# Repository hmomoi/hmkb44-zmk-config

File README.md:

# hmkb44 のページ

44キーのキーボード「hmkb44」の作成資材のページです。

主に、zmkファームウェアの管理と、KiCadの設計資材をおいています。

# 目指すキーボード
* 40%キーボード（EPOMAKER TH40を参考に）
* Bluetoothで接続
* LEDチカチカ
* charlieplexの実験

このくらいを目指して作ってます。
seeeduino_xiao_ble を使ってイロイロ実験してみたくて作成しました。
# レイアウト

# 回路

# 参照したnote
* https://note.com/pooh_polo/n/n2a34a922b4c8 (zmk firmwareの書き方)

# 参照したgithub
* https://github.com/te9no/zmk-config-GeaconSolstice/blob/main/boards/shields/GeaconSolstice/Solstice.keymap
* https://github.com/mctechnology17/zmk-config
* https://github.com/te9no/zmk-config-title72 （charlieplexのダイオードの向きが逆）
* https://github.com/HookyKB/round-robin-schematics (charlieplexのschematicが公開されている)
* https://github.com/mentako-ya/zmk-config-mtk64/tree/master (Layer rgbled widget を参考)

# キーマップ

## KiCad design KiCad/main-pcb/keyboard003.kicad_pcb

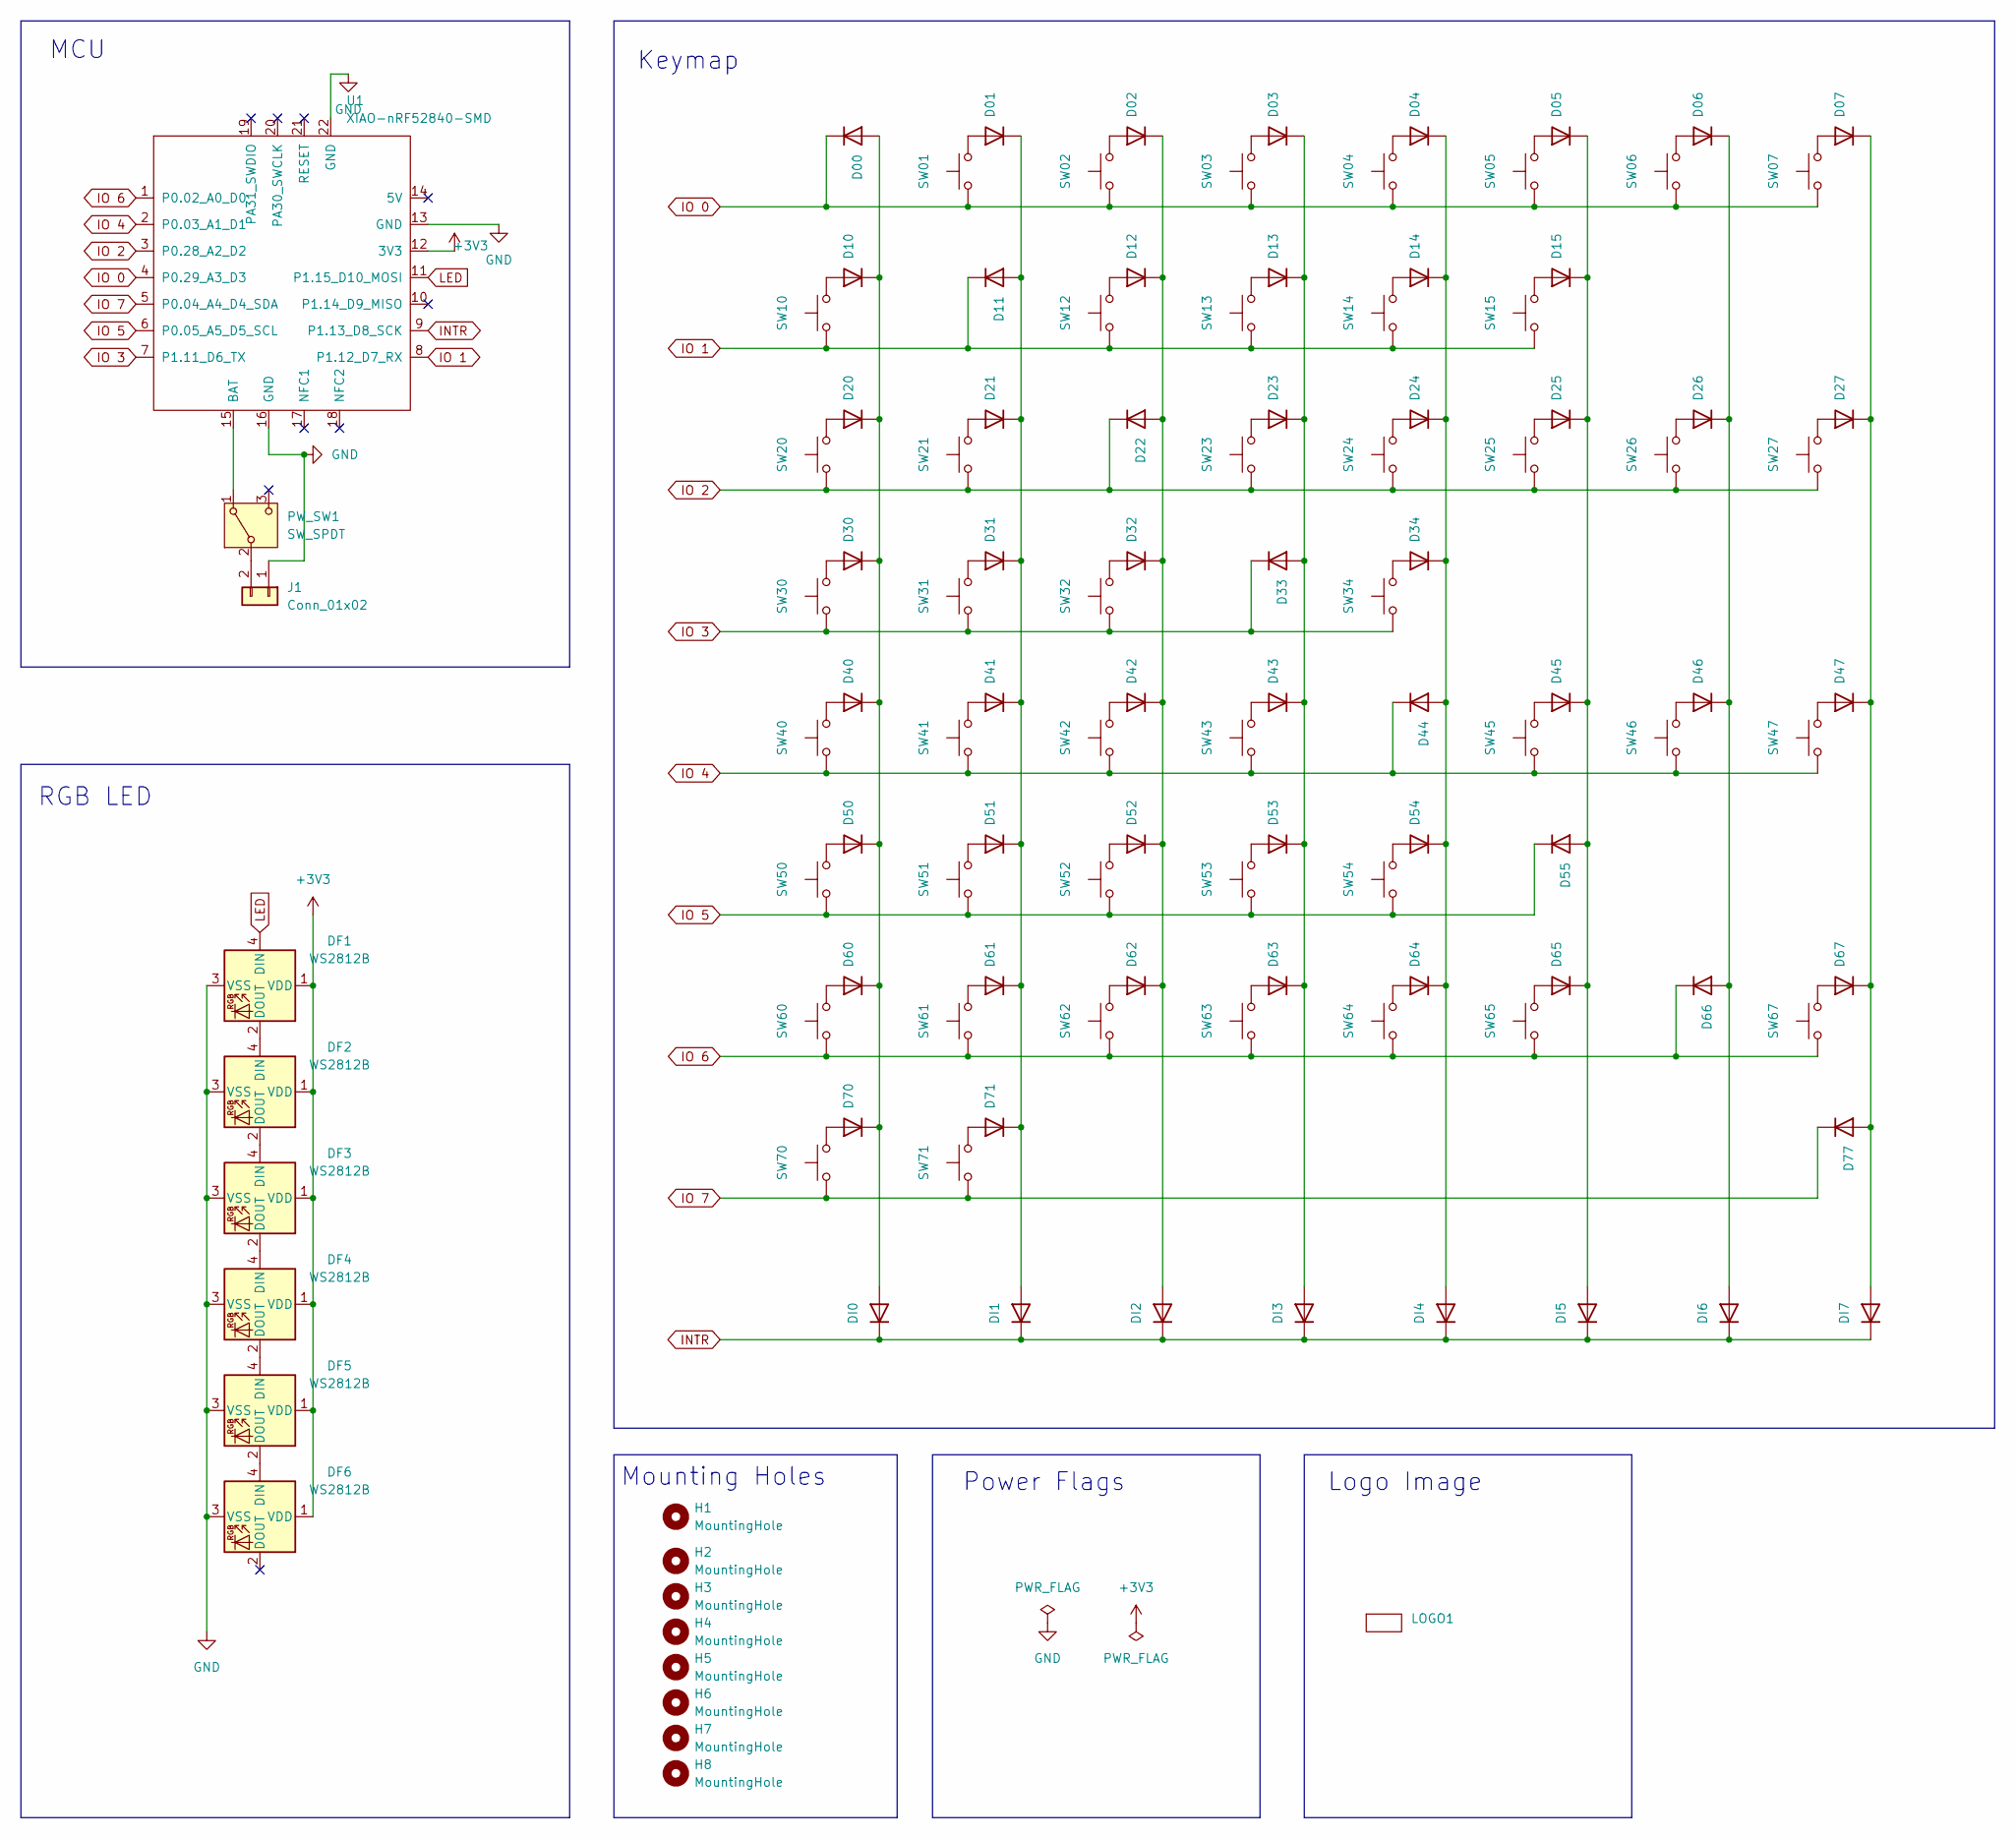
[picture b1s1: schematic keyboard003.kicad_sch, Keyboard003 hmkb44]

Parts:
D00, D01, D02, D03, D04, D05, D06, D07, D10, D11, D12, D13, D14, D15, D20, D21, D22, D23, D24, D25, D26, D27, D30, D31, D32, D33, D34, D40, D41, D42, D43, D44, D45, D46, D47, D50, D51, D52, D53, D54, D55, D60, D61, D62, D63, D64, D65, D66, D67, D70, D71, D77: 1N4148W; D_SOD-123; LCSC C81598
DF1, DF2, DF3, DF4, DF5, DF6: WS2812B; LED_WS2812B_PLCC4_5.0x5.0mm_P3.2mm
DI0, DI1, DI2, DI3, DI4, DI5, DI6, DI7: 1N4148W; D_SOD-123; LCSC C81598
H1, H2, H3, H4, H5, H6, H7, H8: MountingHole; MountingHole_2.2mm_M2
J1: Conn_01x02; JST_PH_S2B-PH-K_1x02_P2.00mm_Horizontal
LOGO1: LOGO
PW_SW1: SW_SPDT; SS-12D01G3
SW01, SW15: SW_Push; CherryMX_Hotswap_1.5u
SW02, SW03, SW04, SW05, SW06, SW07, SW10, SW12, SW13, SW14, SW21, SW23, SW24, SW25, SW26, SW27, SW30, SW31, SW32, SW41, SW42, SW43, SW45, SW46, SW47, SW50, SW51, SW52, SW53, SW64: SW_Push; CherryMX_Hotswap_1u
SW20, SW54: SW_Push; CherryMX_Hotswap_1.75u
SW34, SW63, SW65: SW_Push; CherryMX_Hotswap_2.25u
SW40, SW60, SW61, SW62, SW67, SW70, SW71: SW_Push; CherryMX_Hotswap_1.25u
U1: XIAO-nRF52840-SMD

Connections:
+3V3: DF1.1 (VDD), DF2.1 (VDD), DF3.1 (VDD), DF4.1 (VDD), DF5.1 (VDD), DF6.1 (VDD), U1.12 (3V3)
GND: DF1.3 (VSS), DF2.3 (VSS), DF3.3 (VSS), DF4.3 (VSS), DF5.3 (VSS), DF6.3 (VSS), J1.1, U1.13 (GND), U1.16 (GND), U1.22 (GND)
INTR: DI0.1 (K), DI1.1 (K), DI2.1 (K), DI3.1 (K), DI4.1 (K), DI5.1 (K), DI6.1 (K), DI7.1 (K), U1.9 (P1.13_D8_SCK)
IO 0: D00.1 (K), SW01.1, SW02.1, SW03.1, SW04.1, SW05.1, SW06.1, SW07.1, U1.4 (P0.29_A3_D3)
IO 1: D11.1 (K), SW10.1, SW12.1, SW13.1, SW14.1, SW15.1, U1.8 (P1.12_D7_RX)
IO 2: D22.1 (K), SW20.1, SW21.1, SW23.1, SW24.1, SW25.1, SW26.1, SW27.1, U1.3 (P0.28_A2_D2)
IO 3: D33.1 (K), SW30.1, SW31.1, SW32.1, SW34.1, U1.7 (P1.11_D6_TX)
IO 4: D44.1 (K), SW40.1, SW41.1, SW42.1, SW43.1, SW45.1, SW46.1, SW47.1, U1.2 (P0.03_A1_D1)
IO 5: D55.1 (K), SW50.1, SW51.1, SW52.1, SW53.1, SW54.1, U1.6 (P0.05_A5_D5_SCL)
IO 6: D66.1 (K), SW60.1, SW61.1, SW62.1, SW63.1, SW64.1, SW65.1, SW67.1, U1.1 (P0.02_A0_D0)
IO 7: D77.1 (K), SW70.1, SW71.1, U1.5 (P0.04_A4_D4_SDA)
LED: DF1.4 (DIN), U1.11 (P1.15_D10_MOSI)
unnamed: D00.2 (A), D10.1 (K), D20.1 (K), D30.1 (K), D40.1 (K), D50.1 (K), D60.1 (K), D70.1 (K), DI0.2 (A)
unnamed: D01.2 (A), SW01.2
unnamed: D01.1 (K), D11.2 (A), D21.1 (K), D31.1 (K), D41.1 (K), D51.1 (K), D61.1 (K), D71.1 (K), DI1.2 (A)
unnamed: D02.2 (A), SW02.2
unnamed: D02.1 (K), D12.1 (K), D22.2 (A), D32.1 (K), D42.1 (K), D52.1 (K), D62.1 (K), DI2.2 (A)
unnamed: D03.2 (A), SW03.2
unnamed: D03.1 (K), D13.1 (K), D23.1 (K), D33.2 (A), D43.1 (K), D53.1 (K), D63.1 (K), DI3.2 (A)
unnamed: D04.2 (A), SW04.2
unnamed: D04.1 (K), D14.1 (K), D24.1 (K), D34.1 (K), D44.2 (A), D54.1 (K), D64.1 (K), DI4.2 (A)
unnamed: D05.2 (A), SW05.2
unnamed: D05.1 (K), D15.1 (K), D25.1 (K), D45.1 (K), D55.2 (A), D65.1 (K), DI5.2 (A)
unnamed: D06.2 (A), SW06.2
unnamed: D06.1 (K), D26.1 (K), D46.1 (K), D66.2 (A), DI6.2 (A)
unnamed: D07.2 (A), SW07.2
unnamed: D07.1 (K), D27.1 (K), D47.1 (K), D67.1 (K), D77.2 (A), DI7.2 (A)
unnamed: D10.2 (A), SW10.2
unnamed: D12.2 (A), SW12.2
unnamed: D13.2 (A), SW13.2
unnamed: D14.2 (A), SW14.2
unnamed: D15.2 (A), SW15.2
unnamed: D20.2 (A), SW20.2
unnamed: D21.2 (A), SW21.2
unnamed: D23.2 (A), SW23.2
unnamed: D24.2 (A), SW24.2
unnamed: D25.2 (A), SW25.2
unnamed: D26.2 (A), SW26.2
unnamed: D27.2 (A), SW27.2
unnamed: D30.2 (A), SW30.2
unnamed: D31.2 (A), SW31.2
unnamed: D32.2 (A), SW32.2
unnamed: D34.2 (A), SW34.2
unnamed: D40.2 (A), SW40.2
unnamed: D41.2 (A), SW41.2
unnamed: D42.2 (A), SW42.2
unnamed: D43.2 (A), SW43.2
unnamed: D45.2 (A), SW45.2
unnamed: D46.2 (A), SW46.2
unnamed: D47.2 (A), SW47.2
unnamed: D50.2 (A), SW50.2
unnamed: D51.2 (A), SW51.2
unnamed: D52.2 (A), SW52.2
unnamed: D53.2 (A), SW53.2
unnamed: D54.2 (A), SW54.2
unnamed: D60.2 (A), SW60.2
unnamed: D61.2 (A), SW61.2
unnamed: D62.2 (A), SW62.2
unnamed: D63.2 (A), SW63.2
unnamed: D64.2 (A), SW64.2
unnamed: D65.2 (A), SW65.2
unnamed: D67.2 (A), SW67.2
unnamed: D70.2 (A), SW70.2
unnamed: D71.2 (A), SW71.2
unnamed: DF1.2 (DOUT), DF2.4 (DIN)
unnamed: DF2.2 (DOUT), DF3.4 (DIN)
unnamed: DF3.2 (DOUT), DF4.4 (DIN)
unnamed: DF4.2 (DOUT), DF5.4 (DIN)
unnamed: DF5.2 (DOUT), DF6.4 (DIN)
unnamed: J1.2, PW_SW1.2 (B)
unnamed: PW_SW1.1 (A), U1.15 (BAT)

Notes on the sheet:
MCU
Mounting Holes
RGB LED
Logo Image
Keymap
Power Flags

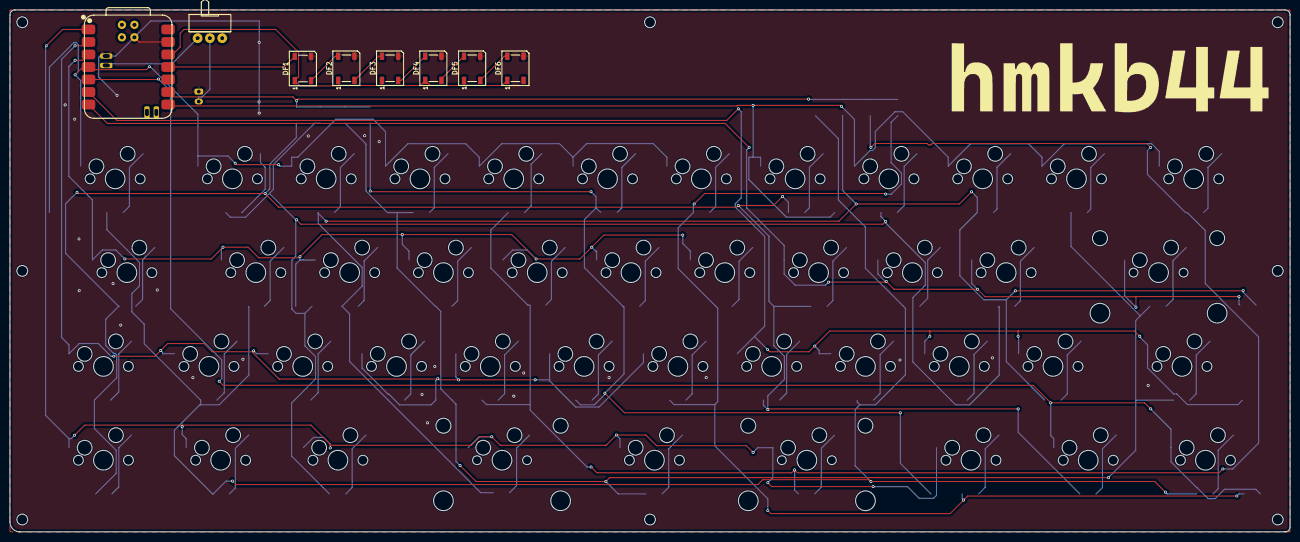
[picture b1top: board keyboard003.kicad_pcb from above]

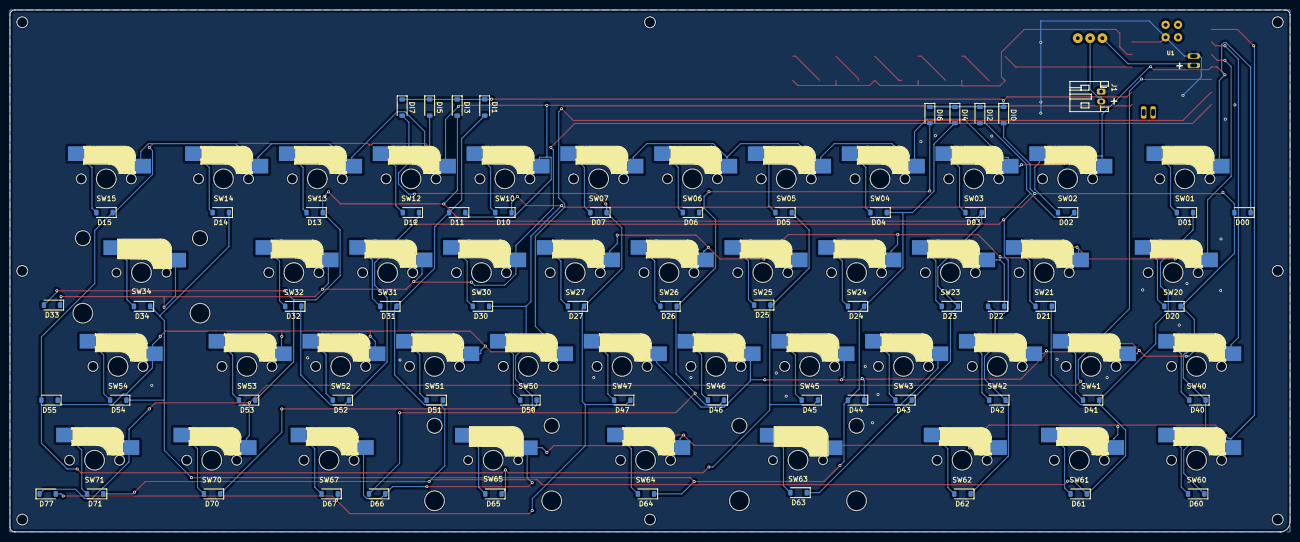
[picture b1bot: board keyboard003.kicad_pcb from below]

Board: 2 copper layers, 260.0 x 106.0 mm, 122 parts (61 on the bottom side), 71 nets.

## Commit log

2025-05-22 testコミット
2025-05-22 サンプルファイル
2025-05-22 hmkb44 First Commit
2025-05-22 yaml commit
2025-05-22 error taiou
2025-05-23 error対応
2025-05-23 エラー対応２
2025-05-23 エラー対応３
2025-05-23 エラー対応４
2025-05-23 エラー対応５
2025-05-23 エラー対応6
2025-05-23 エラー対応７
2025-05-23 エラー対応8
2025-05-23 エラー対応９
2025-05-23 エラー対応10
2025-05-23 layer key change
2025-05-23 tab esc change
2025-05-26 55
    Update README.md
2025-05-26 keymap edit 58
2025-05-26 layer button change 60
2025-05-27 62
    README.mdの変更
    某なれはてさんのページへのリンク追加
2025-05-27 63
    Update README.md
2025-06-07 92
    Update README.md
2025-06-07 93
    Update README.md
2025-06-10 95 改行コードをLFに変更
2025-06-10 96
    Update README.md
2025-06-10 97
    Update README.md
2025-06-12 103
    Update README.md
2025-12-25 [Draw] 173
2025-12-25 Add build workflow for hmkb44 firmware
2025-12-25 [Draw]
2025-12-25 [Draw] 175
2025-12-25 [Draw] 180
2025-12-25 [Draw] Merge branch 'main' of https://github.com/hmomoi/hmkb44-zmk-config
2025-12-25 [Draw] 182
2025-12-25 [Draw] 183
2025-12-25 [Draw] 184
2025-12-25 [Draw] 185
2025-12-25 Add keymap section with image to README
2025-12-26 Replace LGUI with Microsoft Windows key in keymap
2025-12-26 Add LGUI key mapping to config.yaml
2025-12-26 Fix formatting of LGUI entry in config.yaml
2025-12-26 [Draw] Fix formatting of LGUI entry in config.yaml
2025-12-26 Remove LGUI key mapping from config.yaml
    Removed LGUI key mapping from the configuration.
2025-12-26 [Draw] Remove LGUI key mapping from config.yaml
    Removed LGUI key mapping from the configuration.
2025-12-26 [Draw] Add LGUI key mapping to config.yaml
2025-12-27 [Draw] 188
2025-12-27 [Draw] 189
2025-12-27 [Draw] 191
2025-12-27 [Draw] 192
2025-12-27 [Draw] 193
2026-01-04 Update firmware files for branch main
2026-01-20 Add MIT License and attributions to LICENSE file
    Added a LICENSE file detailing the MIT License and third-party components used in the project.
2026-01-20 Update copyright and clean up LICENSE file
    Updated copyright holder in LICENSE file and removed third-party components section.
